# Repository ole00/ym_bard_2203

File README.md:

# ym_bard_2203
A dual YM2203 sound chip board for Arduino Nano

This is an open source/open hardware sound board with two YM2203 FM sound chips driven by Arduino Nano. 
The YM2203 FM chips were used in several arcade game boards made in 80's. 
The design of the YM Bard sound board was actually based on a schematic of an arcade game.

The board allows you to experiment with YM2203 sound chips by writing the chip's register values
from a PC over a serial port. It is also possible to stream an arcade game sound data over
a serial port from a PC based emulator and produce authentic sound and music of an arcade game.

YM2203 chips are register compatible with AY-3 PSG sound generator, therefore you can use FM Bard
to play AY-3 tunes as well.

Arduino selection
----------------------

The b(o)ard requires and Arduino Nano or a NANO clone. You can use 5V Atmel based Arduino Nano
or Renesas based Arduino NANO R4 or 3.3V ESP32-S3 based Arduino NANO or their clones.
The picture above uses a cheap LGT8F328P Nano board.

YM2203 requires an external clock of specific frequency to produce sounds. The clock can 
be generated either by Arduino NANO or by an external Si5351 module connected on the bottom
side of the YM Bard. The Si5351 module is optional, however the Atmel based Arduino NANO can
only produce limited selection of clock frequencies, so it is recommended to use the module 
in such case. NANO R4 and ESP32-S3 based Arduino NANO can produce various frequencies 
and the clock module is not required for driving the FM clock at 3 MHz.

Audio data streaming
----------------------
To stream data to YM Bard use 'ym2203_streamer.ino' Arduino sketch located in 'arduino-src'
subdirectory and upload it to your Arduino NANO. Use Arduino IDE PC software to upload the sketch.
If you use Arduino NANO ESP32-S3 then make sure to install "esp32 by Espressif" version 3.3.X
board support in Arduino IDE Board manager before you do the upload.

The sketch reads binary data sent from the connected PC serial port (115200 baud rate)
and writes the data to the parallel data bus of the FM chips. The stream format supports two types of packets: 
3 byte packet and 12 byte packet.

**3 byte packet**

* 1st byte: bits 7-4: 0xF, bit 3: 0, bits 2-0: chip selection (0 selects the 1st YM2203, 1 selects the 
  2nd YM2203).
* 2nd byte: register address
* 3rd byte: register value

**12 byte packet**
* 1st byte: bits 7-4: 0xF, bit 3: 1, bits 2-0: chip selection (0 selects the 1st YM2203, 1 selects the 
  2nd YM2203).
* byte 2 to byte 12: register values of register 0 to register 10.

3 byte packet allows you to write single arbitrary register. It is flexible, but requires
more data per register to be sent compared to 12 byte packet. 12 byte packets basically sends
multiple PSG registers in one go, saving the serial line bandwidth.

To start streaming open the serial port of your Arduino NANO and write the packets to
the serial port in binary format.

Example playback
-----------------
If you use Linux you can try to connect YM Bard to Ghost'n Goblins arcade emulator located here:

https://github.com/ole00/arcade_emu_gng

Pass the serial port device of the YM Bard to the emulator with parameter '-fm [device name]'
when starting the emulator. For example add '-fm /dev/ttyUSB0' parameter. If your Arduino NANO
has the 'ym2203_streamer.ino' uploaded, then the emulator and connected YM Bard should start
producing tunes from the arcade game.

Board production
------------------
To produce YM Bard you'll need some basic SMT component soldering skills. All components can be
soldered by hand with a modern soldering iron with controllable temperature (like TS100
or similar) set to 330 to 350 deg C. The list of components is located in 'bom_fm_bard_2203.csv'
file. The PCB can be fabricated by jlcpcb.com, pcbway.com, allpcb.com or other online services. 
Use the zip archive stored in the 'gerbers' directory and upload it to the manufacturer's web site
of your choice. Upload the 'ym2203_r2_fab.zip' archive and set the following parameters (if required). 
  
  * 2 layer board
  * PCB Thickness: 1.6, or 1.2 mm
  * Copper Weight: 1
  * The rest of the options can stay default or choose whatever you fancy (colors, finish etc.)

When populating components either start with the smallest SMT parts first (resistors and small capacitors)
or start with the SOIC-8 LM358 OpAmps so that you have plenty of room for the soldering iron tip.
After that, solder the bigger 10uF capacitors - check the capacitor's polarity. The SMT caps use
the stripe on the positive (+) side, the electrolytic TH caps use the stripe on the negative (-) side.
Solder the through hole parts and the audio connector at the end. 
I strongly recommend to use IC sockets for YM2203C chips and also for YM3014B chips.
IC sockets ensure you do not overheat and damage the chips while soldering. They will also allow
you to swap the chip in case you get faulty chips sourced from Aliexpress (not uncommon).

If you are not familiar with SMT soldering check some YT videos and use one of the YM Bard PCB 
as a practice board to solder some SMT resistors and caps. It is not that hard, just requires
good tweezers, use of soldering flux and a bit of practice.

Audio output
--------------
The output audio signal is routed through J1 'mixing' header. The header is supposed to be populated
by jumper caps that connect individual sound sources to either a stereo or mono output. The sound
sources are FM1, PSG1 (both coming from the YM2203 #1) and FM2 and PSG2 (both coming from YM2203 #2).
Yes, YM2203 chips have separate output for FM channels and for the PSG channels. The PSG channel
volume can be adjusted (relatively to the FM channels) by RV1 and RV2 potentiometers.
The middle jumper position on J1 - when shorted - joins all outputs to a mono signal (routed to
both Left and Right audio channel). By default the jumpers are supposed to be all connected (see the 
YM bard image), but you can undo them if you want to disable certain audio sources from the final output. 
Additionally/optionally you might want to design/add a post processing audio option to YM Bard 
by connecting it via J1 and J2 header (has GND and 5V pins). The output is not amplified but
is capable of driving small headphones via J5 headphone socket. If you want louder sound use
PC speakers with an amplifier connected to the headphone socket.

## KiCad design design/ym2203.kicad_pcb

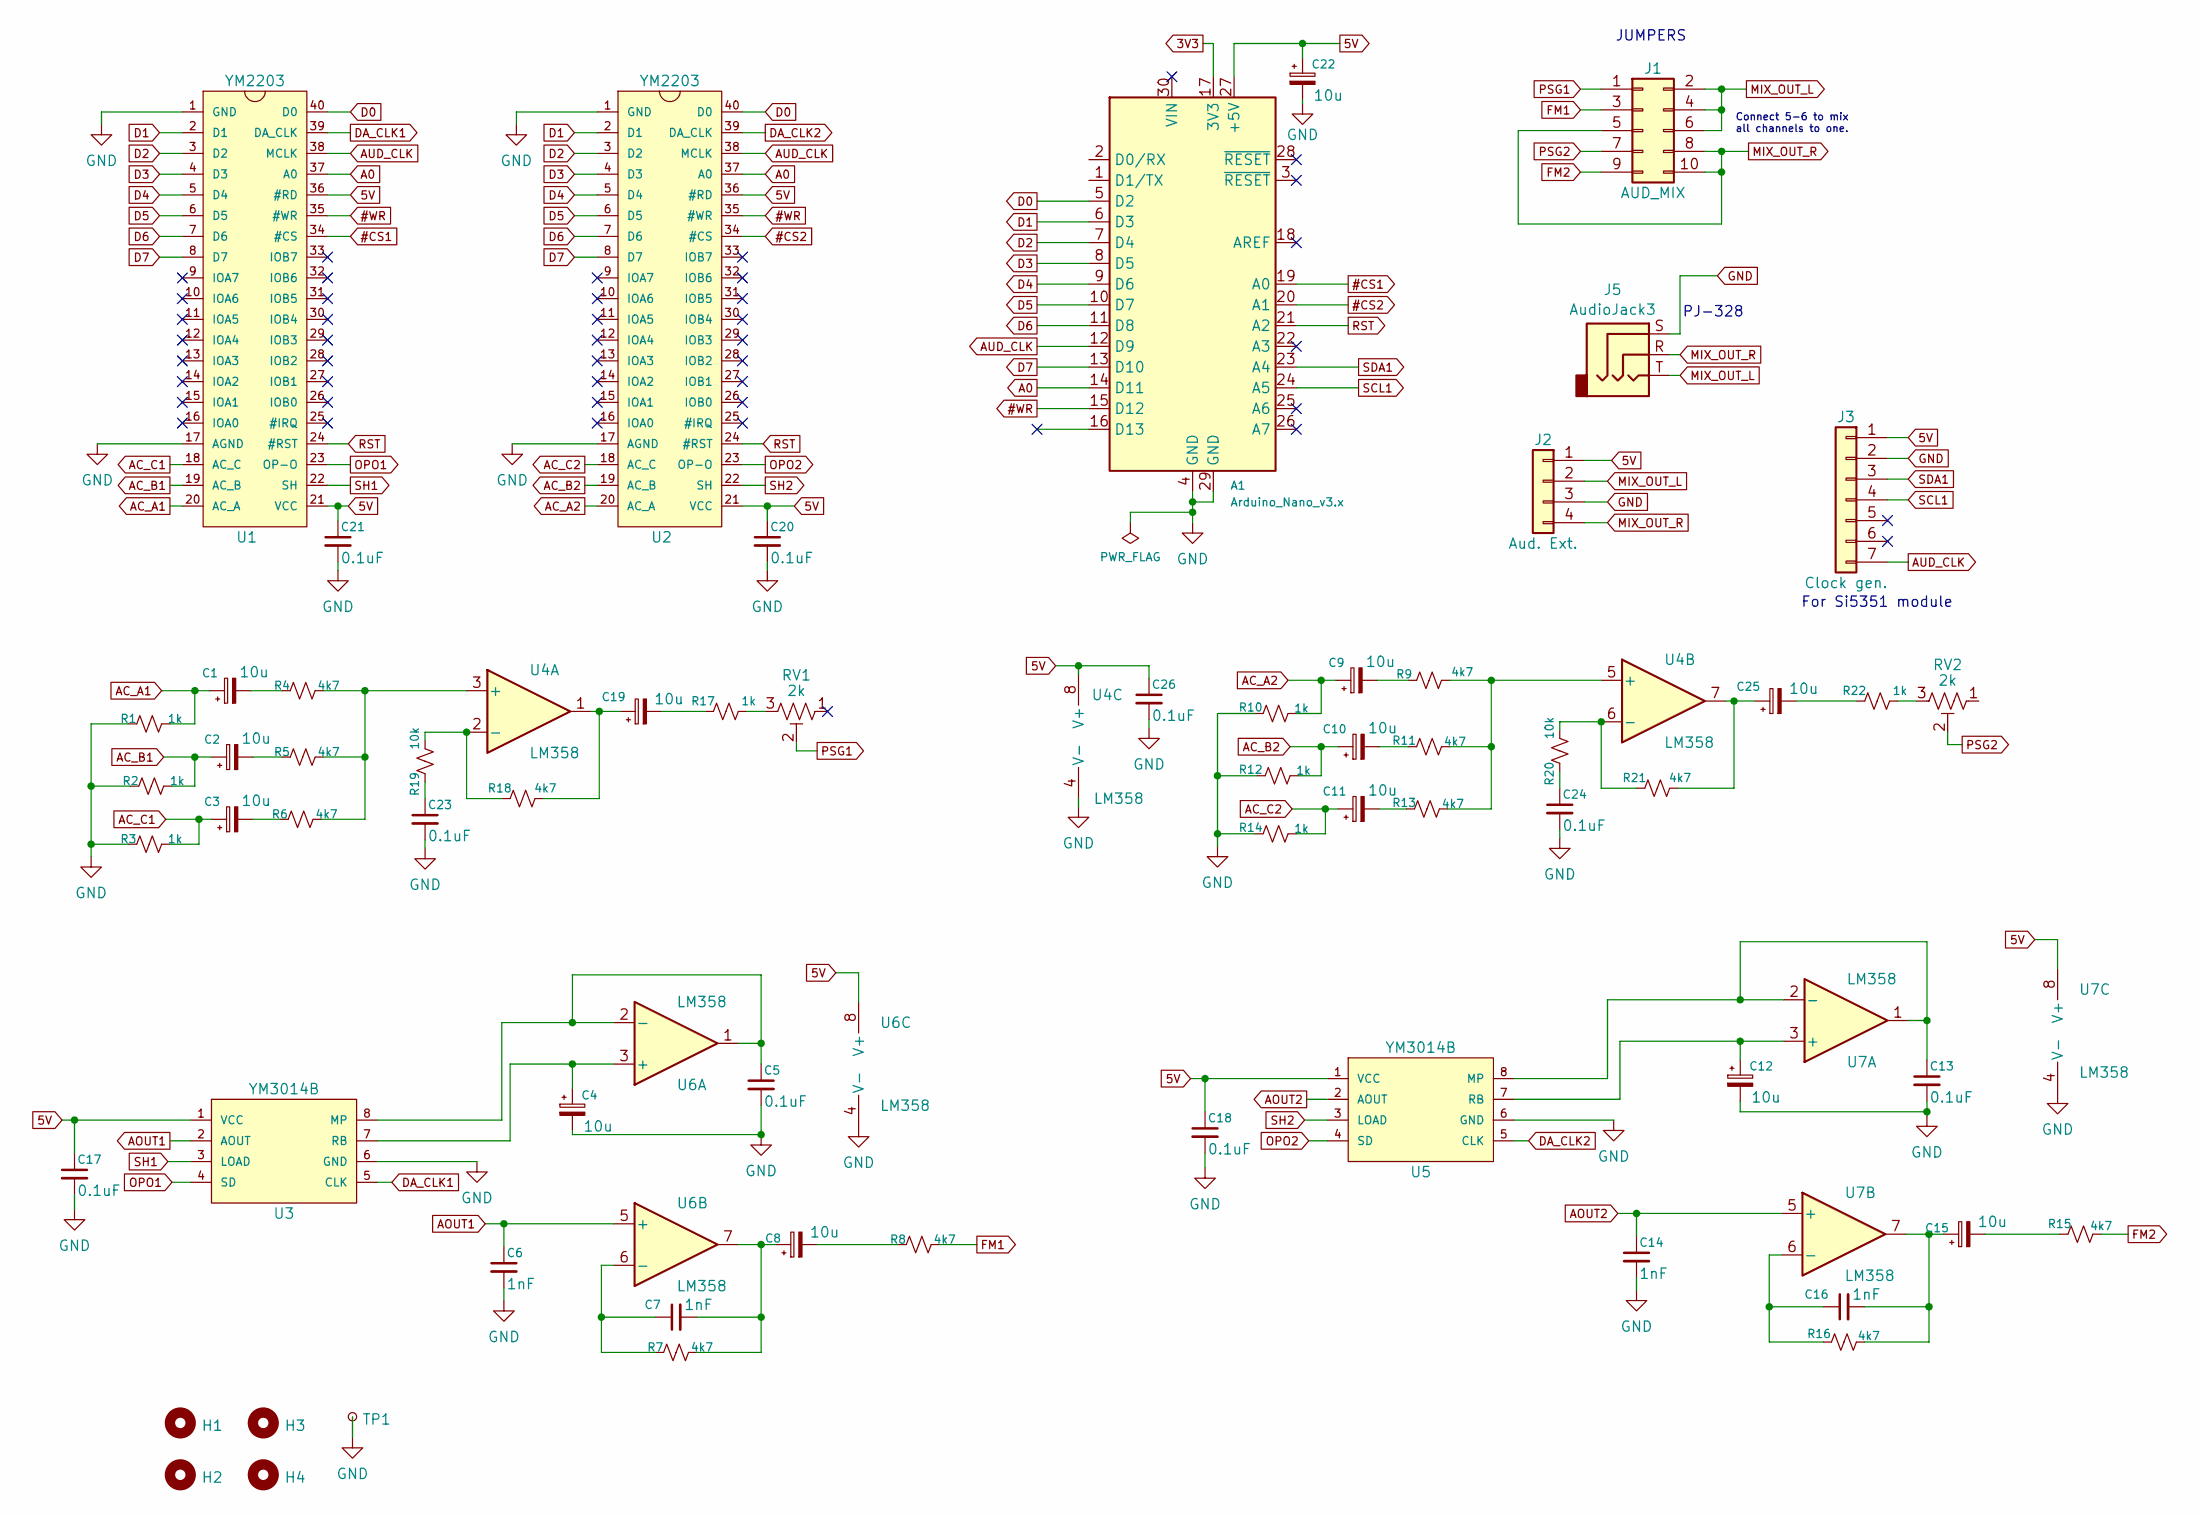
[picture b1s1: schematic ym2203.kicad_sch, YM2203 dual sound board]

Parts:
A1: Arduino_Nano_v3.x; Arduino_Nano_WithMountingHoles
C1, C2, C3, C4, C8, C9, C10, C11, C12, C15, C19, C22, C25: 10u; C_1210_3225Metric_dual_TH
C5, C13, C17, C18, C20, C21, C23, C24, C26: 0.1uF; C_0805_2012Metric_Pad1.18x1.45mm_HandSolder
C6, C7, C14, C16: 1nF; C_0805_2012Metric_Pad1.18x1.45mm_HandSolder
H1, H2, H3, H4: MountingHole; MountingHole_3.2mm_M3
J1: AUD_MIX; PinHeader_2x05_P2.54mm_Vertical
J2: Aud. Ext.; PinSocket_1x04_P2.54mm_Vertical
J3: Clock gen.; pad_array_th_1x07_P2.54mm
J5: AudioJack3; Jack_3.5mm_CUI_SJ2-3593D-SMT_Horizontal
R1, R2, R3, R10, R12, R14, R17, R22: 1k; R_0805_2012Metric_Pad1.20x1.40mm_HandSolder
R4, R5, R6, R7, R8, R9, R11, R13, R15, R16, R18, R21: 4k7; R_0805_2012Metric_Pad1.20x1.40mm_HandSolder
R19, R20: 10k; R_0805_2012Metric_Pad1.20x1.40mm_HandSolder
RV1, RV2: 2k; Potentiometer_Bourns_3339P_Vertical_HandSoldering
TP1: TestPoint_Small; TestPoint_Loop_D2.50mm_Drill1.0mm
U1, U2: YM2203; DIP-40_W15.24mm_LongPads
U3, U5: YM3014B; DIP-8_W7.62mm
U4, U6, U7: LM358; SO-8_5.3x6.2mm_P1.27mm

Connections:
3V3: A1.17 (3V3)
5V: A1.27 (+5V), C17.1, C18.1, C20.1, C21.1, C22.1, C26.1, J2.1, J3.1, U1.21 (VCC), U1.36 (#RD), U2.21 (VCC), U2.36 (#RD), U3.1 (VCC), U4.8 (V+), U5.1 (VCC), U6.8 (V+), U7.8 (V+)
#CS1: A1.19 (A0), U1.34 (#CS)
#CS2: A1.20 (A1), U2.34 (#CS)
#WR: A1.15 (D12), U1.35 (#WR), U2.35 (#WR)
A0: A1.14 (D11), U1.37 (A0), U2.37 (A0)
AC_A1: C1.1, R1.2, U1.20 (AC_A)
AC_A2: C9.1, R10.2, U2.20 (AC_A)
AC_B1: C2.1, R2.2, U1.19 (AC_B)
AC_B2: C10.1, R12.2, U2.19 (AC_B)
AC_C1: C3.1, R3.2, U1.18 (AC_C)
AC_C2: C11.1, R14.2, U2.18 (AC_C)
AOUT1: C6.1, U3.2 (AOUT), U6.5 (+)
AOUT2: C14.1, U5.2 (AOUT), U7.5 (+)
AUD_CLK: A1.12 (D9), J3.7, U1.38 (MCLK), U2.38 (MCLK)
D0: A1.5 (D2), U1.40 (D0), U2.40 (D0)
D1: A1.6 (D3), U1.2 (D1), U2.2 (D1)
D2: A1.7 (D4), U1.3 (D2), U2.3 (D2)
D3: A1.8 (D5), U1.4 (D3), U2.4 (D3)
D4: A1.9 (D6), U1.5 (D4), U2.5 (D4)
D5: A1.10 (D7), U1.6 (D5), U2.6 (D5)
D6: A1.11 (D8), U1.7 (D6), U2.7 (D6)
D7: A1.13 (D10), U1.8 (D7), U2.8 (D7)
DA_CLK1: U1.39 (DA_CLK), U3.5 (CLK)
DA_CLK2: U2.39 (DA_CLK), U5.5 (CLK)
FM1: J1.3, R8.2
FM2: J1.9, R15.2
GND: A1.4 (GND), A1.29 (GND), C4.2, C5.2, C6.2, C12.2, C13.2, C14.2, C17.2, C18.2, C20.2, C21.2, C22.2, C23.2, C24.2, C26.2, J2.3, J3.2, J5.S, R1.1, R2.1, R3.1, R10.1, R12.1, R14.1, TP1.1, U1.1 (GND), U1.17 (AGND), U2.1 (GND), U2.17 (AGND), U3.6 (GND), U4.4 (V-), U5.6 (GND), U6.4 (V-), U7.4 (V-)
MIX_OUT_L: J1.2, J1.4, J1.6, J2.2, J5.T
MIX_OUT_R: J1.5, J1.8, J1.10, J2.4, J5.R
unnamed: C1.2, R4.1
unnamed: C2.2, R5.1
unnamed: C3.2, R6.1
unnamed: C7.2, C8.1, R7.2, U6.7
unnamed: C8.2, R8.1
unnamed: C9.2, R9.1
unnamed: C10.2, R11.1
unnamed: C11.2, R13.1
unnamed: C15.1, C16.2, R16.2, U7.7
unnamed: C15.2, R15.1
unnamed: C19.1, R18.2, U4.1
unnamed: C19.2, R17.1
unnamed: C23.1, R19.1
unnamed: C24.1, R20.1
unnamed: C25.1, R21.2, U4.7
unnamed: C25.2, R22.1
unnamed: R17.2, RV1.3
unnamed: R22.2, RV2.3
unnamed: C5.1, U3.8 (MP), U6.1, U6.2 (-)
unnamed: C4.1, U3.7 (RB), U6.3 (+)
unnamed: R4.2, R5.2, R6.2, U4.3 (+)
unnamed: R18.1, R19.2, U4.2 (-)
unnamed: R9.2, R11.2, R13.2, U4.5 (+)
unnamed: R20.2, R21.1, U4.6 (-)
unnamed: C13.1, U5.8 (MP), U7.1, U7.2 (-)
unnamed: C12.1, U5.7 (RB), U7.3 (+)
unnamed: C7.1, R7.1, U6.6 (-)
unnamed: C16.1, R16.1, U7.6 (-)
OPO1: U1.23 (OP-O), U3.4 (SD)
OPO2: U2.23 (OP-O), U5.4 (SD)
PSG1: J1.1, RV1.2
PSG2: J1.7, RV2.2
RST: A1.21 (A2), U1.24 (#RST), U2.24 (#RST)
SCL1: A1.24 (A5), J3.4
SDA1: A1.23 (A4), J3.3
SH1: U1.22 (SH), U3.3 (LOAD)
SH2: U2.22 (SH), U5.3 (LOAD)

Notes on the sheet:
For Si5351 module
PJ-328
JUMPERS
Connect 5-6 to mix all channels to one.

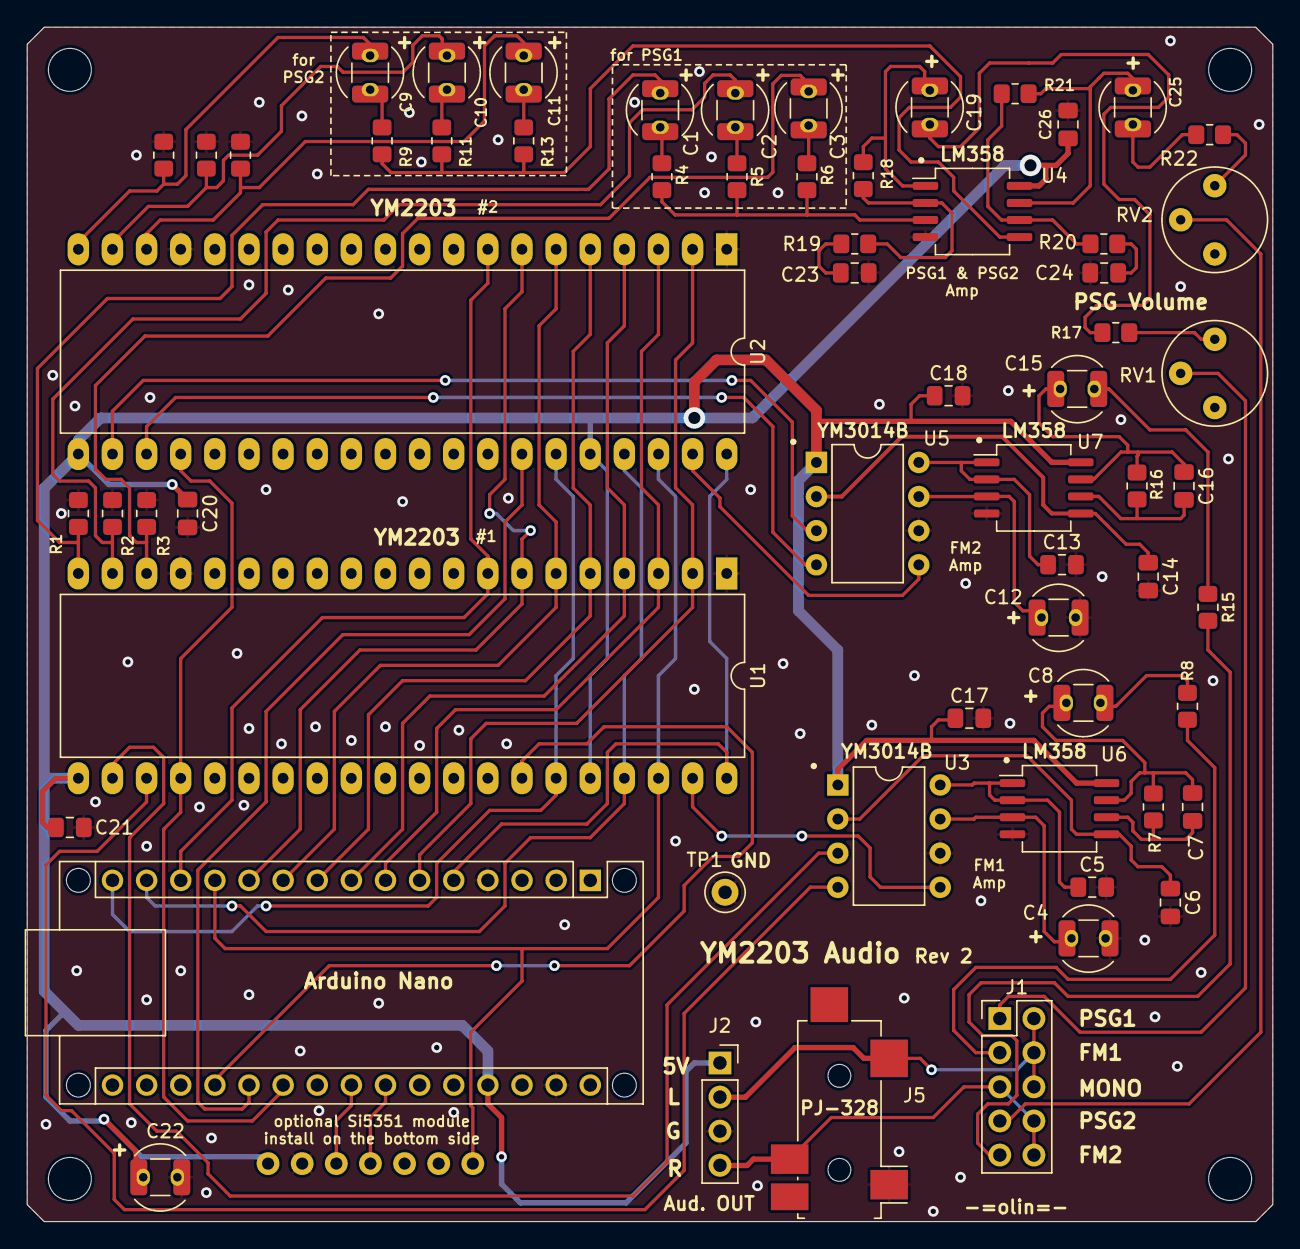
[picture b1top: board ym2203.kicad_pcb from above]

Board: 2 copper layers, 92.7 x 88.9 mm, 67 parts (1 on the bottom side), 66 nets.

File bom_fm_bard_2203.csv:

"Reference","Value","Qty","Notes"
"C1,C2,C3,C4,C8,C9,C10,C11,C12,C15,C19,C22,C25","10uF",13,SMT 1210 or SMT 1208
"C5,C13,C17,C18,C20,C21,C23,C24,C26","0.1uF",9,SMT 0805
"C6,C7,C14,C16","1nF",4,SMT 0805
"J1","AUD_MIX",1,header pin 2x5 2.54mm pin pitch TH
"J5","AudioJack3",1,PJ-328 Audio jack
"R1,R2,R3,R10,R12,R14,R17,R22","1k",8,SMT 0805
"R4,R5,R6,R7,R8,R9,R11,R13,R15,R16,R18,R21","4k7",12,SMT 0805
"R19,R20","10k",2,SMT 0805
"RV1,RV2","2k",2,potentiometer 3362P 2k
"U1,U2","YM2203",2,YM2203C Aliexpress
"U3,U5","YM3014B",2,DAC for Yamaha FM chips
"U4,U6,U7","LM358",3,SMT SOIC-8
"-","jumper cap",5,2.54mm jumper cap (for audio 'mixer')
